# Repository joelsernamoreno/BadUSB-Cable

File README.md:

# BadUSB-Cable
BadUSB cable project

The developers and collaborators of this project do not earn money with this. 
You can invite me for a coffee to further develop Low-Cost hacking devices. If you don't invite me for a coffee, nothing happens, I will continue developing devices.

**Summary:**
1. Evil Crow Cable
2. Evil Crow Cable Pro
3. Evil Crow Cable Wind
4. Collaborators
	
# Evil Crow Cable

* **Start of the project and first BadUSB cable on breadboard (November 2017)**

* **First BadUSB cable with USB connector (December 2017)**

* **Finished proof of concept (January 2018)**

* **Technical presentation of BadUSB cable and first PCB design (Rev0) presented at Hackplayers Conference (February 2018)**

* **Rev1 of BadUSB cable design (January 2019)**

* **Rev2 of BadUSB cable design (May 2019)**

* **First PCBs (July 2019)**

* **BadUSB Cable Rev2 (August 2019)**

* **Rev3 of BadUSB cable design (September 2019)**

* **Development kit (September 2019)**

* **BadUSB Cable Rev3 (September 2019)**

* **Development kits and complete cables for Navaja Negra Conference (October 2019)**

* **Rev3.1 of BadUSB Cable design (October 2019)**

This version is a solution for Rev3. Rev3 has the holes D- and D+, these holes should NOT be soldered and Rev3 can be confusing.
In Rev3.1 design these holes are eliminated, only VDD and GND are available.
Thanks to @_MG_ for recommending this solution.

* **Evil Crow Cable (November 2019)**

**PROJECT REPOSITORY:** https://github.com/joelsernamoreno/EvilCrow-Cable

# Evil Crow Cable Pro

* **First test PCB with USB Hub for testing microcontrollers (March 2020)**

* **First PoC - Atmega32U4 and Hub USB (June 2020)**

* **First PCB - Atmega32U4 and Hub USB (September 2020)**

* **Second PoC Rev1 - RP2040 (April 2023)**

* **Second PoC Rev2 - RP2040 (April 2023)**

* **Second PoC Rev3 - RP2040 (May 2023)**

* **Second PCB - RP2040 (June 2023)**

* **Second PoC Rev4 - RP2040 and USB Host pads (July 2023)**

* **Final PCB - RP2040 and USB Host pads (August 2023)**

* **Evil Crow Cable Pro (August 2023)**

**PROJECT REPOSITORY:** https://github.com/joelsernamoreno/EvilCrowCable-Pro

# Evil Crow Cable Wind

* **First PoC - Atmega32U4 and ESP8285 (May 2020)**

* **Second PoC - ESP8285 (July 2020)**

* **First PCBs - ESP8285 (August 2020)**

* **Third PoC - ESP32-S2 (September 2022)**

* **First PCB - ESP32-S2 (September 2022)**

* **Final PoC Rev 1 - ESP32-C3 inside a USB Type-C connector (June 2024)**

* **Final PCB Rev 1 - ESP32-C3 inside a USB Type-C connector (July 2024)**

* **Final PoC Rev 2 - ESP32-S3 inside a USB Type-C connector (August 2024)**

* **Final PCB - Evil Crow Cable Wind (August 2024)**

**PROJECT REPOSITORY:** https://github.com/joelsernamoreno/EvilCrowCable-Wind

# Collaborators

**Ignacio Diaz & Forensic Security:**

	* Ignacio Díaz: @Nacon_96

	* Forensic & Security: @ForensicSec

	* https://forensic-security.com

**April Brother:**

	* April Brother: @aprbrother

	* https://www.aprbrother.com

**Ernesto Xload:**

	* Ernesto Xload: @ernesto_xload

**Jorge Mata:**

	* Jorge Mata: @jor_mata

	* Innovart: @innovart_cc

	* https://innovart.cc

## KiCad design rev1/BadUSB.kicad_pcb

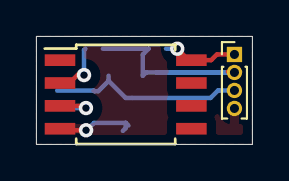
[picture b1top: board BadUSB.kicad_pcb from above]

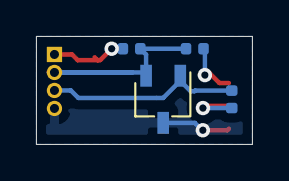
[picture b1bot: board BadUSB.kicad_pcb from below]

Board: 2 copper layers, 12.0 x 6.0 mm, 6 parts (4 on the bottom side), 6 nets.

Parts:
D1: D_Zener_x2_ACom_KKA; TSOT-23
J1: USB_A; PinHeader_1x04_P1.00mm_Vertical
R1, R2: 68R; R_0402_1005Metric
R3: 1K5; R_0402_1005Metric
U1: ATtiny85V-10SU; SOIJ-8_5.3x5.3mm_P1.27mm

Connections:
+D: D1.1, J1.3, R1.2
+V: J1.1, R3.1, U1.8
-D: D1.2, J1.2, R2.2, R3.2
GND: D1.3, J1.4, U1.4
unnamed: R1.1, U1.3
unnamed: R2.1, U1.2

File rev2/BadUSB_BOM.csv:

"Id";"Identificador";"Empaquetado";"Cantidad";"Identificación";"Suministrador y ref";
1;"J1";"pads_badusb";1;"USB_A";;;
2;"U1";"SOIJ-8_5.3x5.3mm_P1.27mm";1;"ATtiny85V-10SU";;;
3;"R1,R2";"R_0402_1005Metric";2;"68R";;;
4;"R3";"R_0402_1005Metric";1;"1K5";;;
5;"D1";"TSOT-23";1;"D_Zener_x2_ACom_KKA";;;

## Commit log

2019-08-08 BadUSB Cable
2019-08-08 README.md
2019-09-18 Installation
2019-10-08 Documentation
2019-10-09 gerbers rev3 and rev3.1
2024-08-02 Add Evil Crow Cable
2024-08-02 Add Evil Crow Cable Pro
2024-08-02 Add Evil Crow Cable Wind
